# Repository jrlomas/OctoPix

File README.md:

# OctoPix Expansion PCB for BTT Octopus Board

This PCB expansion board adds additional Neopixel outputs to your BTT Octopus board, allowing for custom RGB lighting configurations. It plugs into the Octopus's SPI3 header (J47) and provides four JST-XH 3-pin connectors to support up to four separate Neopixel connections.

## Features

- **4x JST-XH 3-pin connectors** for Neopixel data connections
- Compatible with the **BTT Octopus** control board for 3D printers
- Designed to plug directly into the **SPI3 (J47)** header on the Octopus
- Compact design fits neatly without obstructing other ports or components on the Octopus board
- **Buffered data signals** using a **CD4050B** (DIP 16 package) for reliable Neopixel communication

## Bill of Materials (BOM)

| Quantity | Part Description                                      | Example Sourcing Links                                                                                                          |
|----------|-------------------------------------------------------|-----------------------------------------------------------------------------------------------------------------------|
| 4        | JST-XH 3-pin connectors                               |   [DigiKey](https://www.digikey.com/en/products/detail/jst-sales-america-inc/B3B-XH-A/1651046)                                                                                                                    |
| 1        | 2x5 header, 2.54mm pitch (Sullins SFH11-PBPC-D05-RA-BK) | [DigiKey SFH11-PBPC-D05-RA-BK](https://www.digikey.com/en/products/detail/sullins-connector-solutions/SFH11-PBPC-D05-RA-BK/1990095) |
| 1        | CD4050B (DIP 16 package)                              |   [DigiKey](https://www.digikey.com/en/products/detail/texas-instruments/CD4050BE/67303)                                                                                                                    |

## Installation

1. Align the OctoPix PCB with the **J47 SPI3 header** on the Octopus board.
2. Gently press the OctoPix PCB into the J47 header until fully seated.
3. Connect your Neopixel strips to the 3-pin JST-XH connectors on the OctoPix PCB.
4. Power on your Octopus board and configure your Neopixel effects using your preferred firmware (e.g., Klipper, Marlin).

**OctoPix PCB Installed on BTT Octopus Board** (front and rear views):

## Known Issues & Solutions

Some users have reported the isssue that when assigning PB3, PB4, and PB5 to neopixels, klipper reports the pins as already being assigned to ``spi3`` (specially in STM32F446 MCUs).
If you get this problem when restarting klipper, the solution is to recompile klipper firmware commenting out the lines below, found in the source code under ``~/klipper/src/stm32/spi.c``:

```
 DECL_ENUMERATION("spi_bus", "spi3", 4);
 DECL_CONSTANT_STR("BUS_PINS_spi3", "PB4,PB5,PB3");
```

The lines should instead read:

```
//DECL_ENUMERATION("spi_bus", "spi3", 4);
//DECL_CONSTANT_STR("BUS_PINS_spi3", "PB4,PB5,PB3");
```

After re-compiling and flashing the Octopus, PB3, PB4, and PB5 should be free to be used as GPIO pins instead of being bound to ``spi3``

## Credits

This project was created by **knight_rad.iant** on Discord. Join the discussion and follow updates on the design.

---

Contributions, suggestions, and improvements are welcome. Please open an issue or submit a pull request if you have ideas to enhance this project.

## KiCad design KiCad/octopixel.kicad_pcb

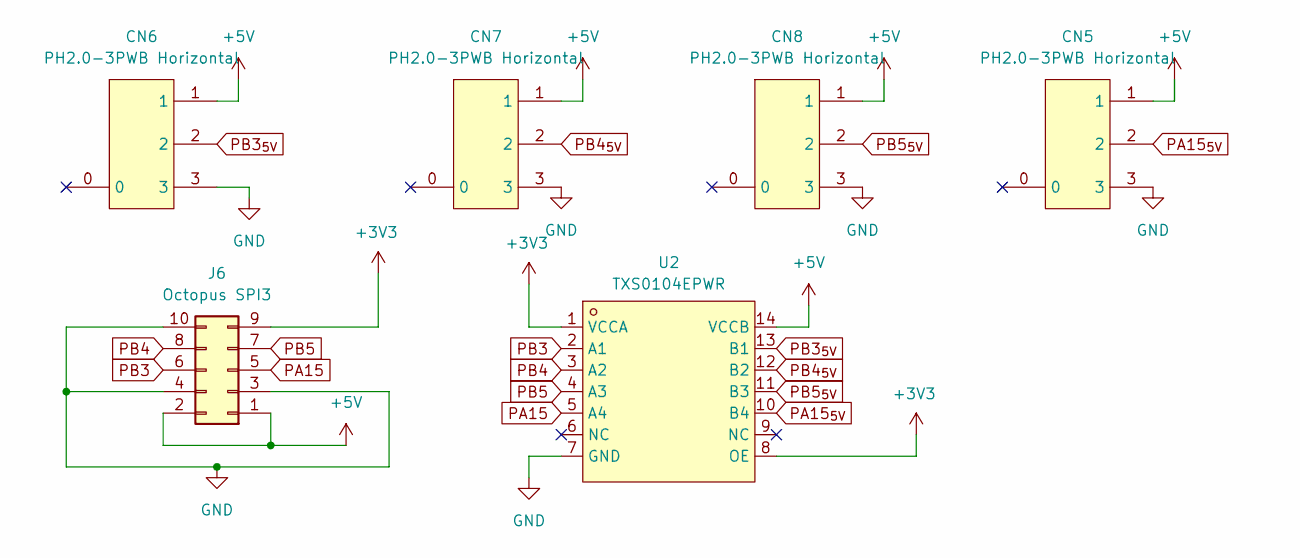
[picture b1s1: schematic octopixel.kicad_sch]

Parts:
CN5, CN6, CN7, CN8: PH2.0-3PWB Horizontal; CONN-TH_PH-3PWB; LCSC Part C81626
J6: Octopus SPI3; PinSocket_2x05_P2.54mm_Horizontal
U2: TXS0104EPWR; TSSOP-14_L5.0-W4.4-P0.65-LS6.4-BL; LCSC Part C44955

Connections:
+3V3: J6.9, U2.1 (VCCA), U2.8 (OE)
+5V: CN5.1, CN6.1, CN7.1, CN8.1, J6.1, J6.2, U2.14 (VCCB)
GND: CN5.3, CN6.3, CN7.3, CN8.3, J6.3, J6.4, J6.10, U2.7 (GND)
PA15: J6.5, U2.5 (A4)
PA15_{5V}: CN5.2, U2.10 (B4)
PB3: J6.6, U2.2 (A1)
PB3_{5V}: CN6.2, U2.13 (B1)
PB4: J6.8, U2.3 (A2)
PB4_{5V}: CN7.2, U2.12 (B2)
PB5: J6.7, U2.4 (A3)
PB5_{5V}: CN8.2, U2.11 (B3)

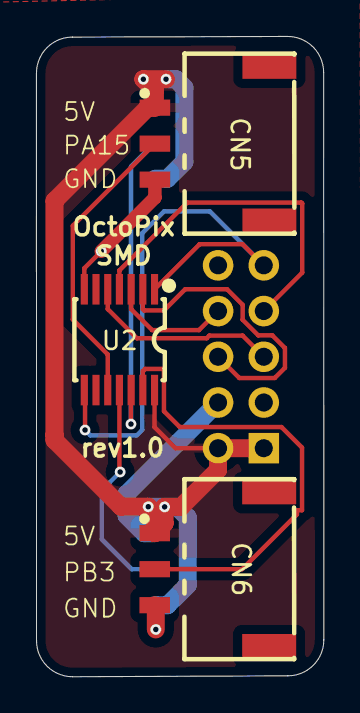
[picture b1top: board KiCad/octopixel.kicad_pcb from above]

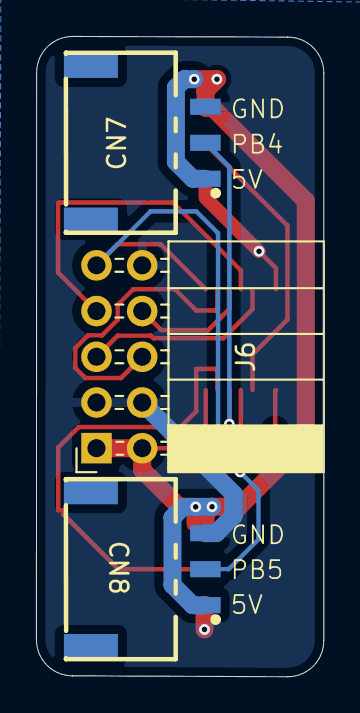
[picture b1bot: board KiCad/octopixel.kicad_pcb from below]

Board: 2 copper layers, 16.0 x 35.6 mm, 6 parts (3 on the bottom side), 11 nets.

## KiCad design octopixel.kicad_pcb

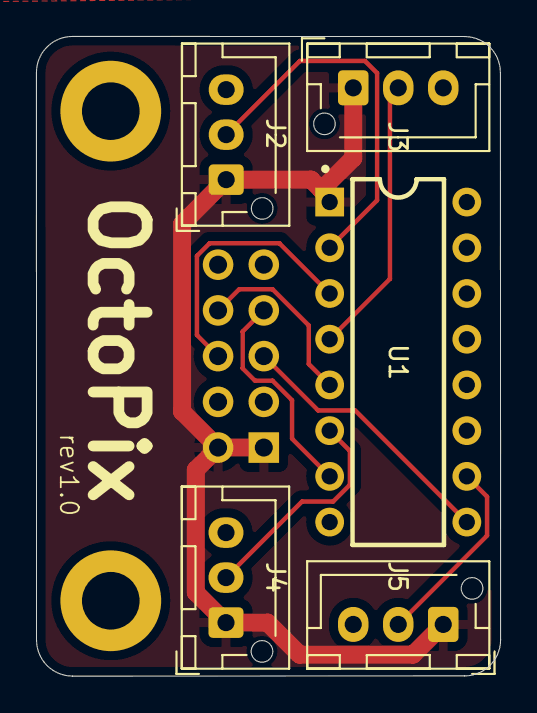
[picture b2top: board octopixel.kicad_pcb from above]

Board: 2 copper layers, 25.8 x 35.5 mm, 8 parts (1 on the bottom side), 10 nets.

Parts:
H1, H2: MountingHole; MountingHole_3.2mm_M3_DIN965_Pad
J2: RBG PB3; JST_XH_B3B-XH-AM_1x03_P2.50mm_Vertical
J3: RBG PB4; JST_XH_B3B-XH-AM_1x03_P2.50mm_Vertical
J4: RBG PB5; JST_XH_B3B-XH-AM_1x03_P2.50mm_Vertical
J5: RBG_PB3; JST_XH_B3B-XH-AM_1x03_P2.50mm_Vertical
J6: Octopus SPI3; PinSocket_2x05_P2.54mm_Horizontal
U1: CD4050BE; DIP-16_L20.3-W10.2-P2.54-LS10.2-BL

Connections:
+5V: J2.1, J3.1, J4.1, J5.1, J6.1, J6.2, U1.1 (VCC)
GND: J2.3, J3.3, J4.3, J5.3, J6.3, J6.4, J6.10, U1.8 (VSS)
PA15: J6.5, U1.9 (D)
PA15_{5V}: J5.2, U1.10 (J=D)
PB3: J6.6, U1.3 (A)
PB3_{5V}: J2.2, U1.2 (G=A)
PB4: J6.8, U1.5 (B)
PB4_{5V}: J3.2, U1.4 (H=B)
PB5: J6.7, U1.7 (C)
PB5_{5V}: J4.2, U1.6 (I=C)

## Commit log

2024-10-26 OctoPix initial commit
2024-10-26 Added .gitignore
2024-10-26 Added license
2024-10-26 Updated step file
2024-10-26 Reorganization of project
2024-10-26 Intial commit for SMD version
2024-11-15 Included missing grounds for connectors
